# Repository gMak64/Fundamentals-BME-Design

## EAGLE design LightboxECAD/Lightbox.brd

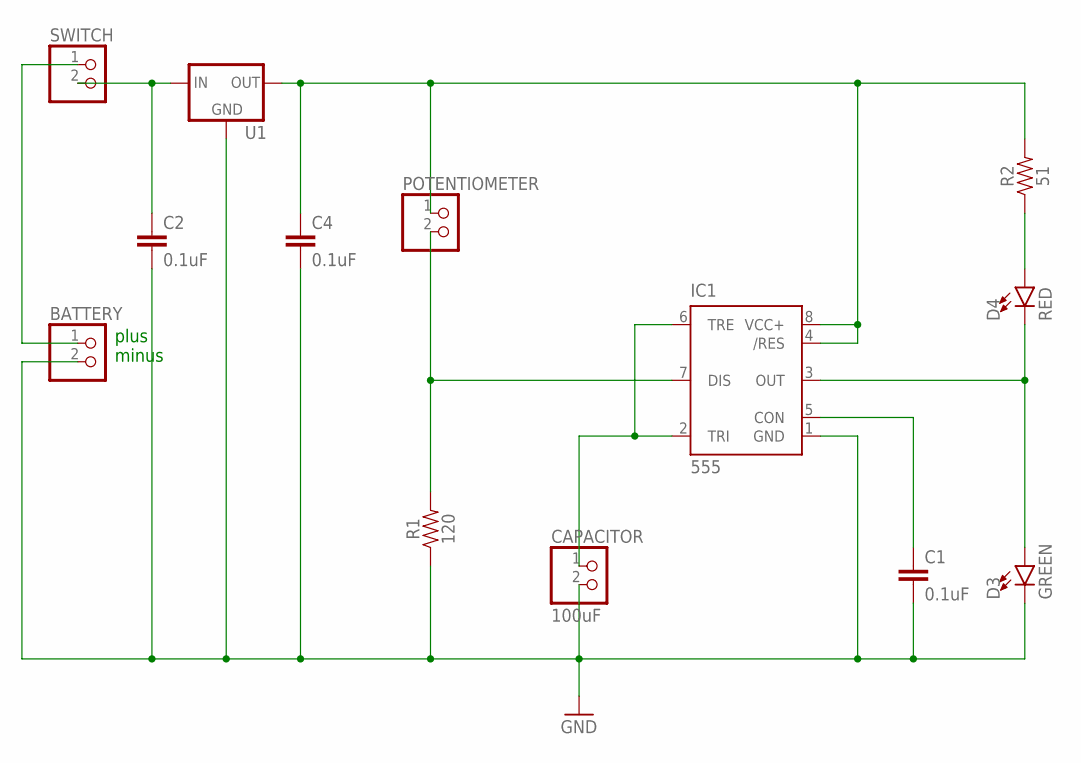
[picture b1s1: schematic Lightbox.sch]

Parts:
BATTERY: PINHD-1X2; 1X02
C1, C2, C4: 0.1uF; 0402
CAPACITOR: 100uF; 1X02
D3: GREEN; LED-1206
D4: RED; LED-1206
IC1: 555; DIP08
POTENTIOMETER: PINHD-1X2; 1X02
R1: 120; 0603
R2: 51; 0603
SWITCH: PINHD-1X2; 1X02
U1: V_REG_78XX-TO-220; TO-220-ALT

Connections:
GND: BATTERY.2, C1.2, C2.2, C4.2, CAPACITOR.2, D3.C, IC1.1 (GND), R1.1, U1.GND
unnamed: C2.1, SWITCH.2, U1.IN
unnamed: D4.A, R2.1
unnamed: C1.1, IC1.5 (CON)
unnamed: CAPACITOR.1, IC1.2 (TRI), IC1.6 (TRE)
unnamed: IC1.7 (DIS), POTENTIOMETER.2, R1.2
unnamed: C4.1, IC1.4 (/RES), IC1.8 (VCC+), POTENTIOMETER.1, R2.2, U1.OUT
unnamed: BATTERY.1, SWITCH.1
unnamed: D3.A, D4.C, IC1.3 (OUT)

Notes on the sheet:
plus minus

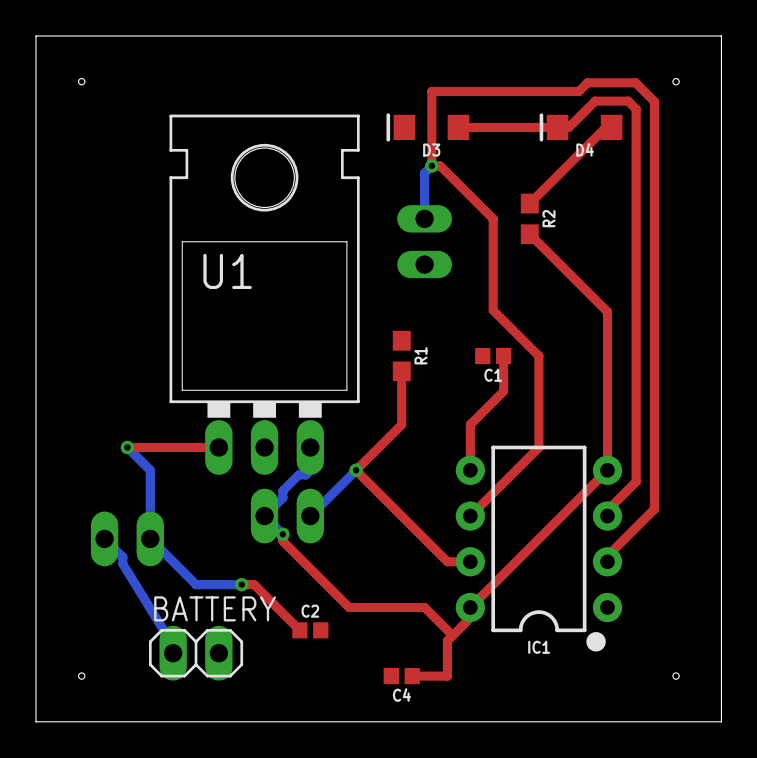
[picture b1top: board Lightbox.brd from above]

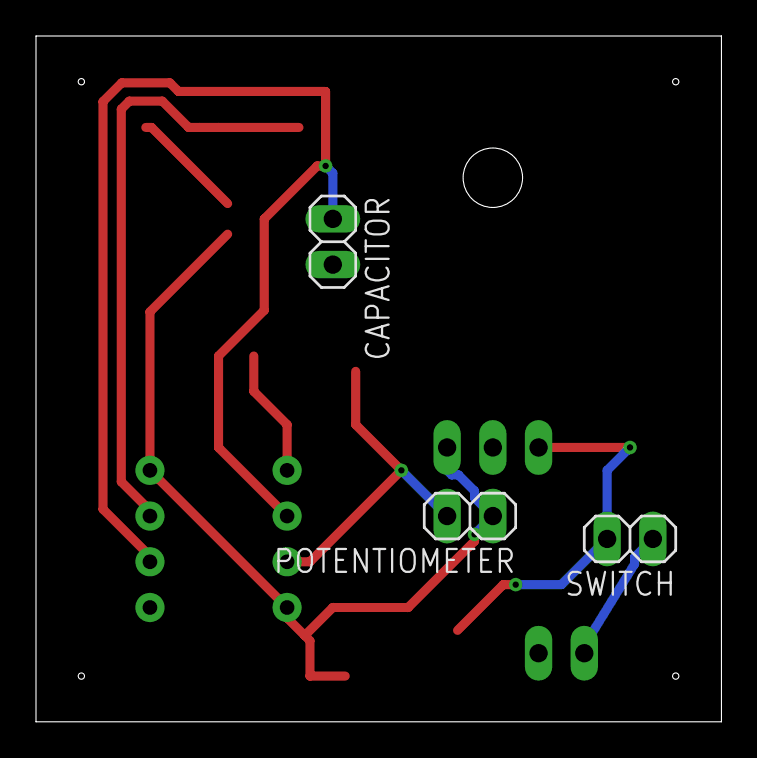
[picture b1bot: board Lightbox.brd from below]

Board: 2 copper layers, 38.1 x 38.1 mm, 13 parts (3 on the bottom side), 9 nets.

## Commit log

2019-02-01 Frequency Finder
2019-02-01 Added code to solve for resistance
2019-02-04 Schematics added

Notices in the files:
parts and their libraries:
SparkFun-Capacitors: Licensing: Creative Commons ShareAlike 4.0 International - https://creativecommons.org/licenses/by-sa/4.0
